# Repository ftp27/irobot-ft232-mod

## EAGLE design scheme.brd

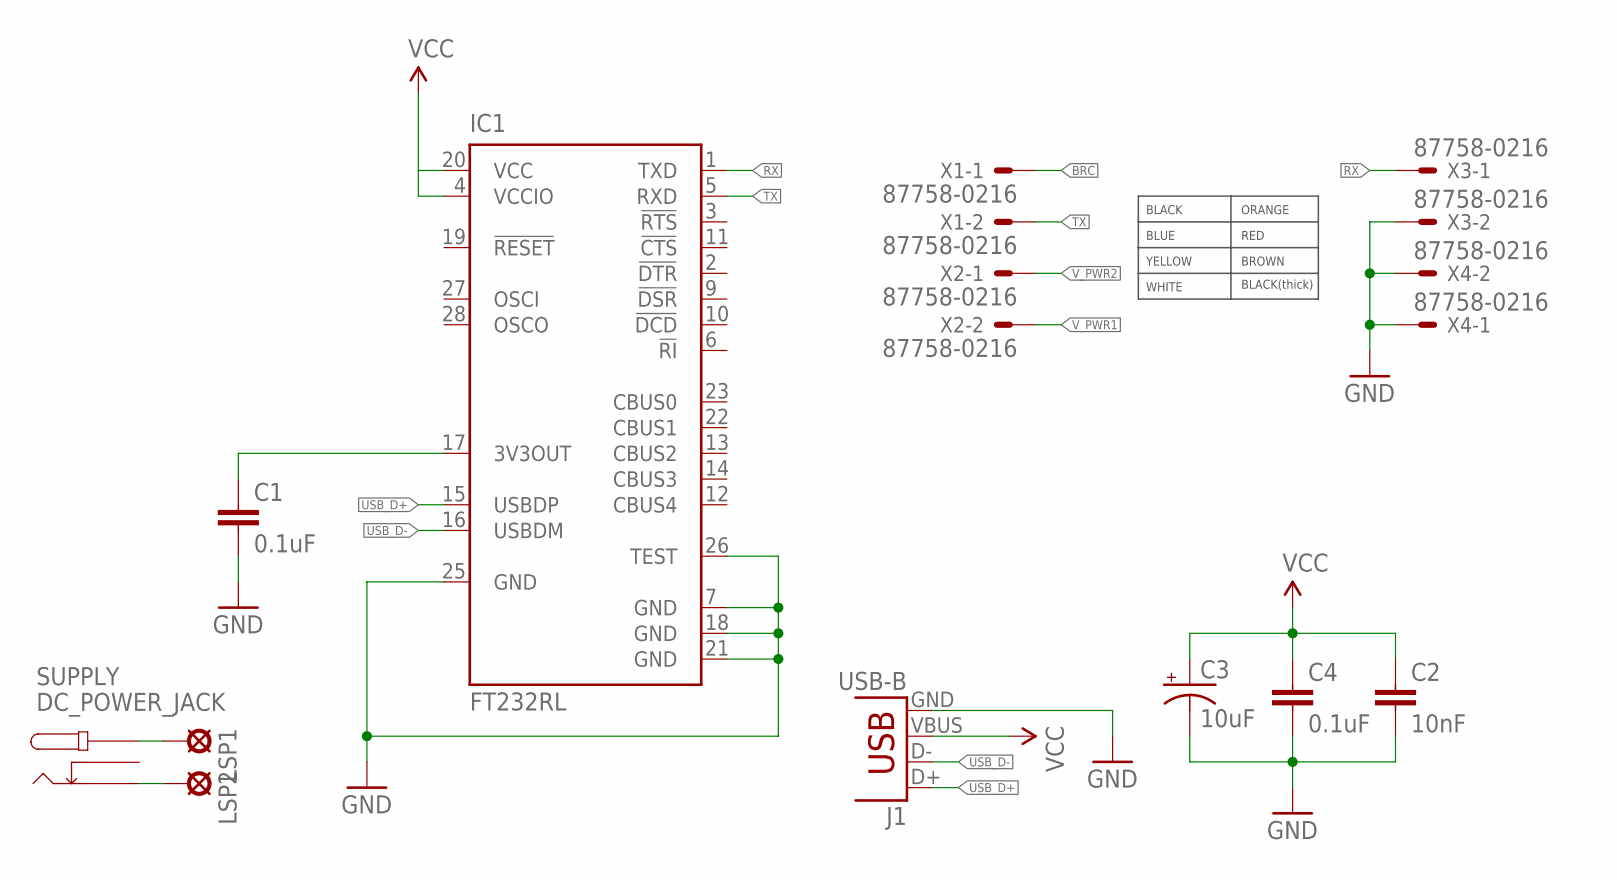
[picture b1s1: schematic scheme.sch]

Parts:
C1, C4: 0.1uF; C0805K
C2: 10nF; C0805K
C3: 10uF; EIA3216-KIT
IC1: FT232RL; SSOP28
J1: USB-B; USB-B-PTH
LSP1, LSP2: SE14
SUPPLY: DC_POWER_JACK
X1, X2, X3, X4: 87758-0216

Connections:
BRC: X1.1
GND: C1.2, C2.2, C3.C (-), C4.2, IC1.7 (GND), IC1.18 (GND), IC1.21 (GND), IC1.25 (GND), IC1.26 (TEST), J1.GND, X3.2, X4.1, X4.2
unnamed: LSP1.MP, SUPPLY.P1
unnamed: LSP2.MP, SUPPLY.P2
unnamed: C1.1, IC1.17 (3V3OUT)
P3: SUPPLY.P3
RX: IC1.1 (TXD), X3.1
TX: IC1.5 (RXD), X1.2
USB_D+: IC1.15 (USBDP), J1.D+
USB_D-: IC1.16 (USBDM), J1.D-
VCC: C2.1, C3.A (+), C4.1, IC1.4 (VCCIO), IC1.20 (VCC), J1.VBUS
V_PWR1: X2.2
V_PWR2: X2.1

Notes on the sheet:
BLACK(thick)
WHITE
YELLOW
BLUE
BROWN
RED
ORANGE
BLACK

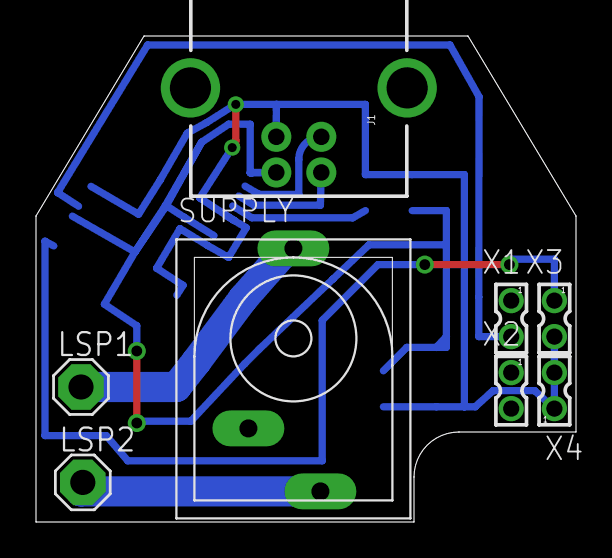
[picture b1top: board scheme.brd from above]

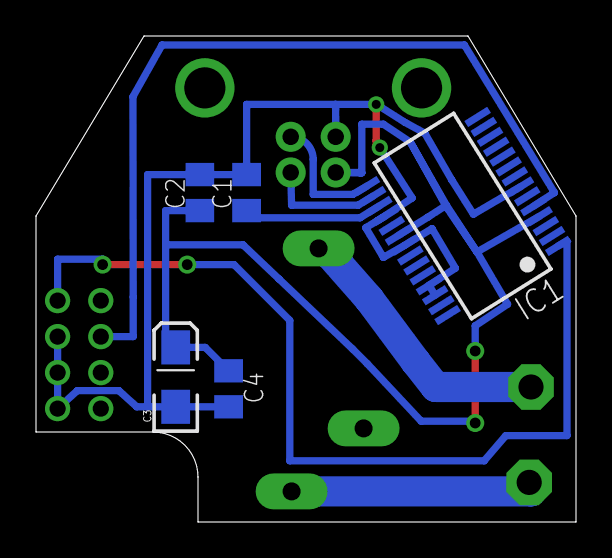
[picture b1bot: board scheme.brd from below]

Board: 2 copper layers, 30.0 x 27.0 mm, 13 parts (5 on the bottom side), 9 nets.

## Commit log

2016-02-07 Add gitignore
2016-02-07 Add power-jack
2016-02-07 Add power jack to scheme
2016-02-08 Done scheme
2016-02-09 Add brd file
2016-02-09 finished brd
2016-02-09 Position changes in brd
2016-02-10 changed brd

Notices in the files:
parts and their libraries:
SparkFun-Capacitors: Licensing: Creative Commons ShareAlike 4.0 International - https://creativecommons.org/licenses/by-sa/4.0
